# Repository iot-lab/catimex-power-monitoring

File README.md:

# Catimex: Hardware

Custom developer board for measure the power consumption of a load connected in either the USB connector or in the HOUT header connector.

## Overview
This folder contains the necessary files to replicate the custom board develop for catimex project. This board has the following features:
* [STM32F103RE Microcontroller](https://www.st.com/en/microcontrollers/stm32f103re.html)
* [FT2232H USB Bridge](https://www.ftdichip.com/Support/Documents/DataSheets/ICs/DS_FT2232H.pdf)
* [INA226 Power monitor](http://www.ti.com/product/INA226)

The board has two different power supply, one for the load (open-node) and other for the main microcontroller (control-node). In the picture below, the micro usb connector of the open node is marked in blue, while the connector for the control node is marked in a red rectangle.

In this version the jumper in 3V3 must be placed to power the control node.

## How to use

### Power the board
#### From a usb port
To measure the power consumption of any load, connect two micro usb ports to each connector. The control node will send the information through serial port so you need to connect this to a pc. On the other side you can power the open node from a pc usb port or any other source.

#### From an external source
If you do not want to connect the control node to a pc, you can connect a battery in the JST connector on the board and access to serial port through the pin headers exposed on the board.

### Connect the load
The load or open-node should be connected in the usb connector or in the HOUT header connector. Once plug in you should start to receive the measurement of bus voltage and current used by the board.

### Power Supply and Start-up Considerations
The board available connectors are:
* USBCN : USB connector for the control node. If connected the control node is power up and you will be able to receive through serial console.
* USBON : USB connector for power up and interact with any node connected, in this case the open node.
* USB : USB port to connect a external node, as in this case the open node
* HOUT : Header to power an external node (open node) from a header connector instead of using the USB port above.
* BAT : Header connector to plug any external battery for the open node, instead of use USBON connection.
* BAT-JST : JST connector to plug in an external battery
* 3V3_IN : Feed the control node from the on-board voltage regulator and USBCN. A jumper has to be connecting both pins in order to power the control node from USB port. Note: This was build for development purposes.

The pinout configuration is in the image below:

## Need features
From the different test made, there are the following missing features:
* Add 2 LEDs to the board
* Add an OFF state for power the open node
* Match I2C port for INA226 with current in FIT IoTLab and the ALERT interrupt pin
* Add a battery charger
* Be able to put a 802.15.4 radio on top
* Expose same pins as the control node in FIT
* Be able to measure voltage of battery

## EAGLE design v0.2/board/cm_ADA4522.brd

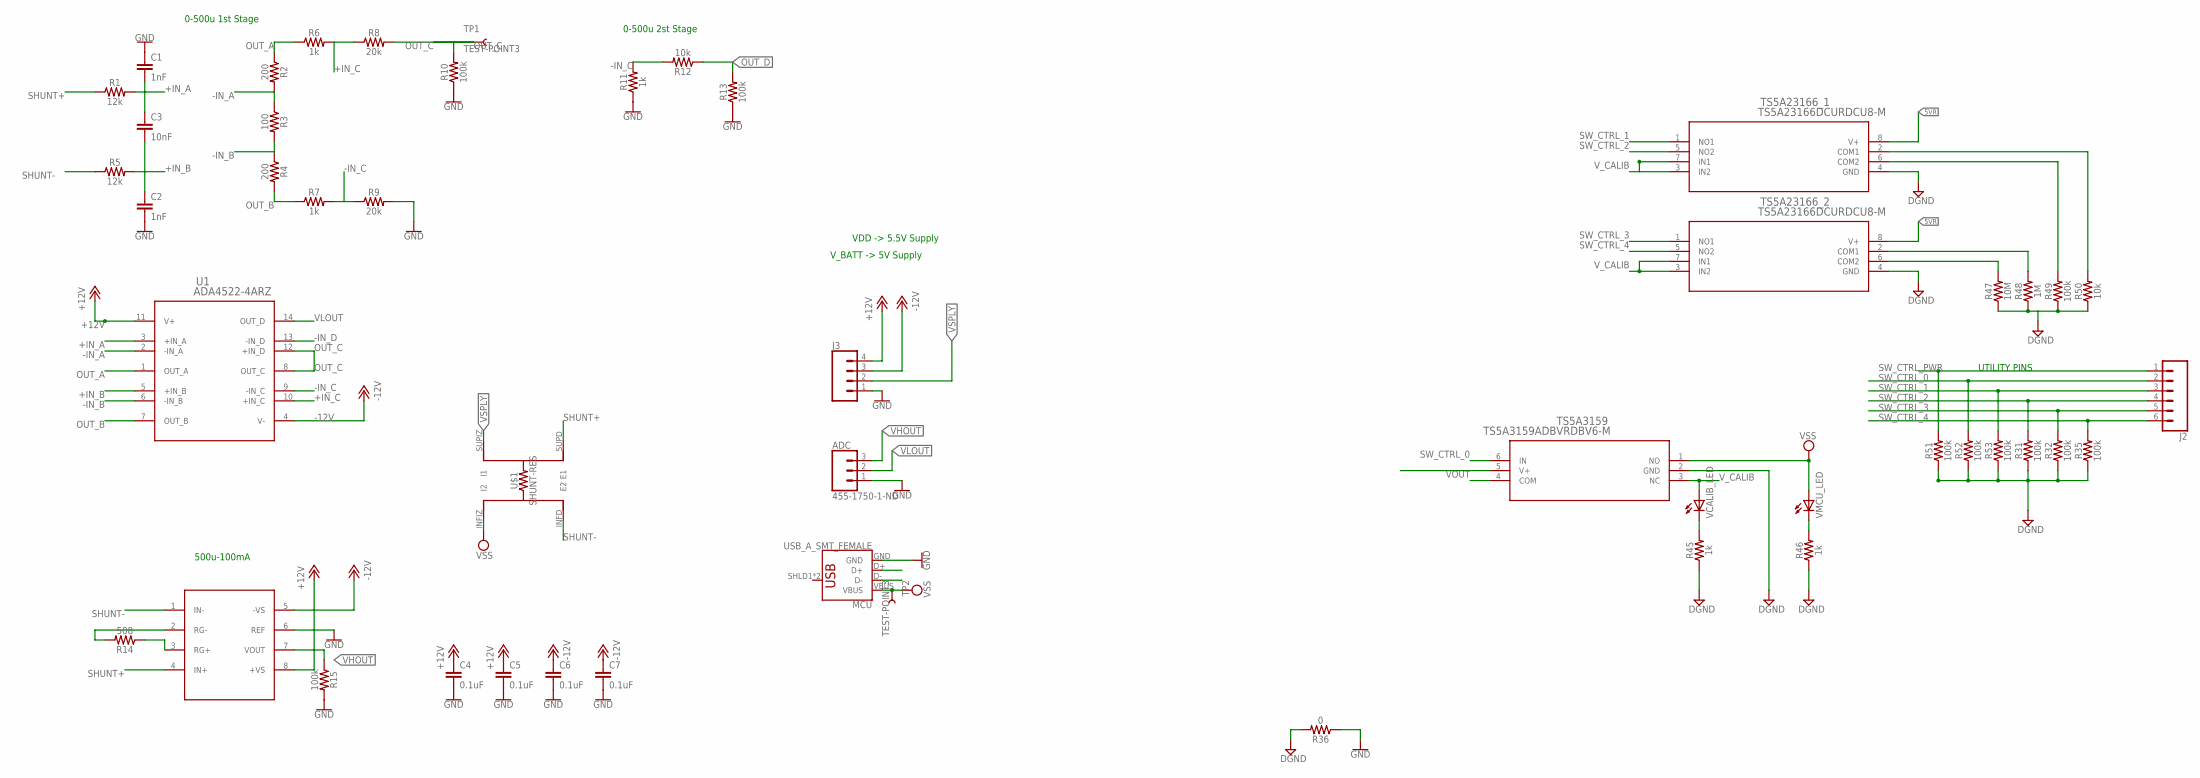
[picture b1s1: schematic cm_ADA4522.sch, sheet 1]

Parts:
AD8422: AD8422; SO08
ADC: 455-1750-1-ND; 1X03
C1, C2: 1nF; 0603
C3: 10nF; 0603
C4, C5, C6, C7: 0.1uF; 0603
J2: CONN_06LONGPADS; 1X06_LONGPADS
J3: CONN_04; 1X04
MCU: USB_A_SMT_FEMALE; USB-A-S-SILK-FEMALE
R1, R5: 12k; 0603
R2, R4: 200; 0603
R3: 100; 0603
R6, R7, R11, R45, R46: 1k; 0603
R8, R9: 20k; 0603
R10, R13, R15, R31, R32, R35, R49, R51, R52, R53: 100k; 0603
R12, R50: 10k; 0603
R14: 508; 0603
R36: 0; 0603
R47: 10M; 0603
R48: 1M; 0603
TP1, TP2: TEST-POINT3; PAD.03X.03
TS5A3159: TS5A3159ADBVRDBV6-M; DBV6-M
TS5A23166_1, TS5A23166_2: TS5A23166DCURDCU8-M; DCU8-M
U1: ADA4522-4ARZ; R_14
U$1: SHUNT-RES; HIPREC-SMD-SHUNT
VCALIB_LED: LEDCHIPLED_0603; CHIPLED_0603
VMCU_LED: LEDCHIPLED_0603; CHIPLED_0603

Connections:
5VR: TS5A23166_1.8 (V+), TS5A23166_2.8 (V+); also elsewhere on the board
5V_F: TS5A3159.5 (V+)
+12V: AD8422.8 (+VS), C4.1, C5.1, J3.4, U1.11 (V+); also elsewhere on the board
+IN_A: C1.2, C3.1, R1.2, U1.3 (+IN_A)
+IN_B: C2.1, C3.2, R5.2, U1.5 (+IN_B)
+IN_C: R6.2, R8.1, U1.10 (+IN_C)
-12V: AD8422.5 (-VS), C6.1, C7.1, J3.3, U1.4 (V-); also elsewhere on the board
-IN_A: R2.2, R3.1, U1.2 (-IN_A)
-IN_B: R3.2, R4.1, U1.6 (-IN_B)
-IN_C: R7.2, R9.1, R11.2, R12.2, U1.9 (-IN_C)
-IN_D: U1.13 (-IN_D)
DGND: R31.1, R32.1, R35.1, R36.2, R45.1, R46.1, R47.1, R48.1, R49.1, R50.1, R51.1, R52.1, R53.1, TS5A3159.2 (GND), TS5A23166_1.4 (GND), TS5A23166_2.4 (GND); also elsewhere on the board
GND: AD8422.6 (REF), ADC.1, C1.1, C2.2, C4.2, C5.2, C6.2, C7.2, J3.1, MCU.GND, R9.2, R10.1, R11.1, R13.1, R15.2, R36.1; also elsewhere on the board
unnamed: AD8422.2 (RG-), R14.2
unnamed: AD8422.3 (RG+), R14.1
unnamed 36: R45.2, VCALIB_LED.C; also elsewhere on the board
unnamed 37: R46.2, VMCU_LED.C; also elsewhere on the board
unnamed: R50.2, TS5A23166_1.2 (COM1)
unnamed: R49.2, TS5A23166_1.6 (COM2)
unnamed: R48.2, TS5A23166_2.2 (COM1)
unnamed: R47.2, TS5A23166_2.6 (COM2)
OUT_A: R2.1, R6.1, U1.1 (OUT_A)
OUT_B: R4.2, R7.1, U1.7 (OUT_B)
OUT_C: R8.2, R10.2, TP1.P$1, U1.8 (OUT_C), U1.12 (+IN_D)
OUT_D: R12.1, R13.2
SHUNT+: AD8422.4 (IN+), R1.1, U$1.SUPD (E1)
SHUNT-: AD8422.1 (IN-), R5.1, U$1.INFD (E2)
SW_CTRL_0: J2.2, R52.2, TS5A3159.6 (IN); also elsewhere on the board
SW_CTRL_1: J2.3, R53.2, TS5A23166_1.1 (NO1); also elsewhere on the board
SW_CTRL_2: J2.4, R31.2, TS5A23166_1.5 (NO2); also elsewhere on the board
SW_CTRL_3: J2.5, R32.2, TS5A23166_2.1 (NO1); also elsewhere on the board
SW_CTRL_4: J2.6, R35.2, TS5A23166_2.5 (NO2); also elsewhere on the board
SW_CTRL_PWR: J2.1, R51.2; also elsewhere on the board
VHOUT: AD8422.7 (VOUT), ADC.3, R15.1
VLOUT: ADC.2, U1.14 (OUT_D)
VOUT: TS5A3159.4 (COM)
VSPLY: J3.2, U$1.SUPIZ (I1); also elsewhere on the board
VSS: MCU.VBUS, TP2.P$1, TS5A3159.1 (NO), U$1.INFIZ (I2), VMCU_LED.A; also elsewhere on the board
V_CALIB: TS5A3159.3 (NC), TS5A23166_1.3 (IN2), TS5A23166_1.7 (IN1), TS5A23166_2.3 (IN2), TS5A23166_2.7 (IN1), VCALIB_LED.A; also elsewhere on the board

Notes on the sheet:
0-500u 1st Stage
500u-100mA
0-500u 2st Stage
VDD -> 5.5V Supply
V_BATT -> 5V Supply
UTILITY PINS

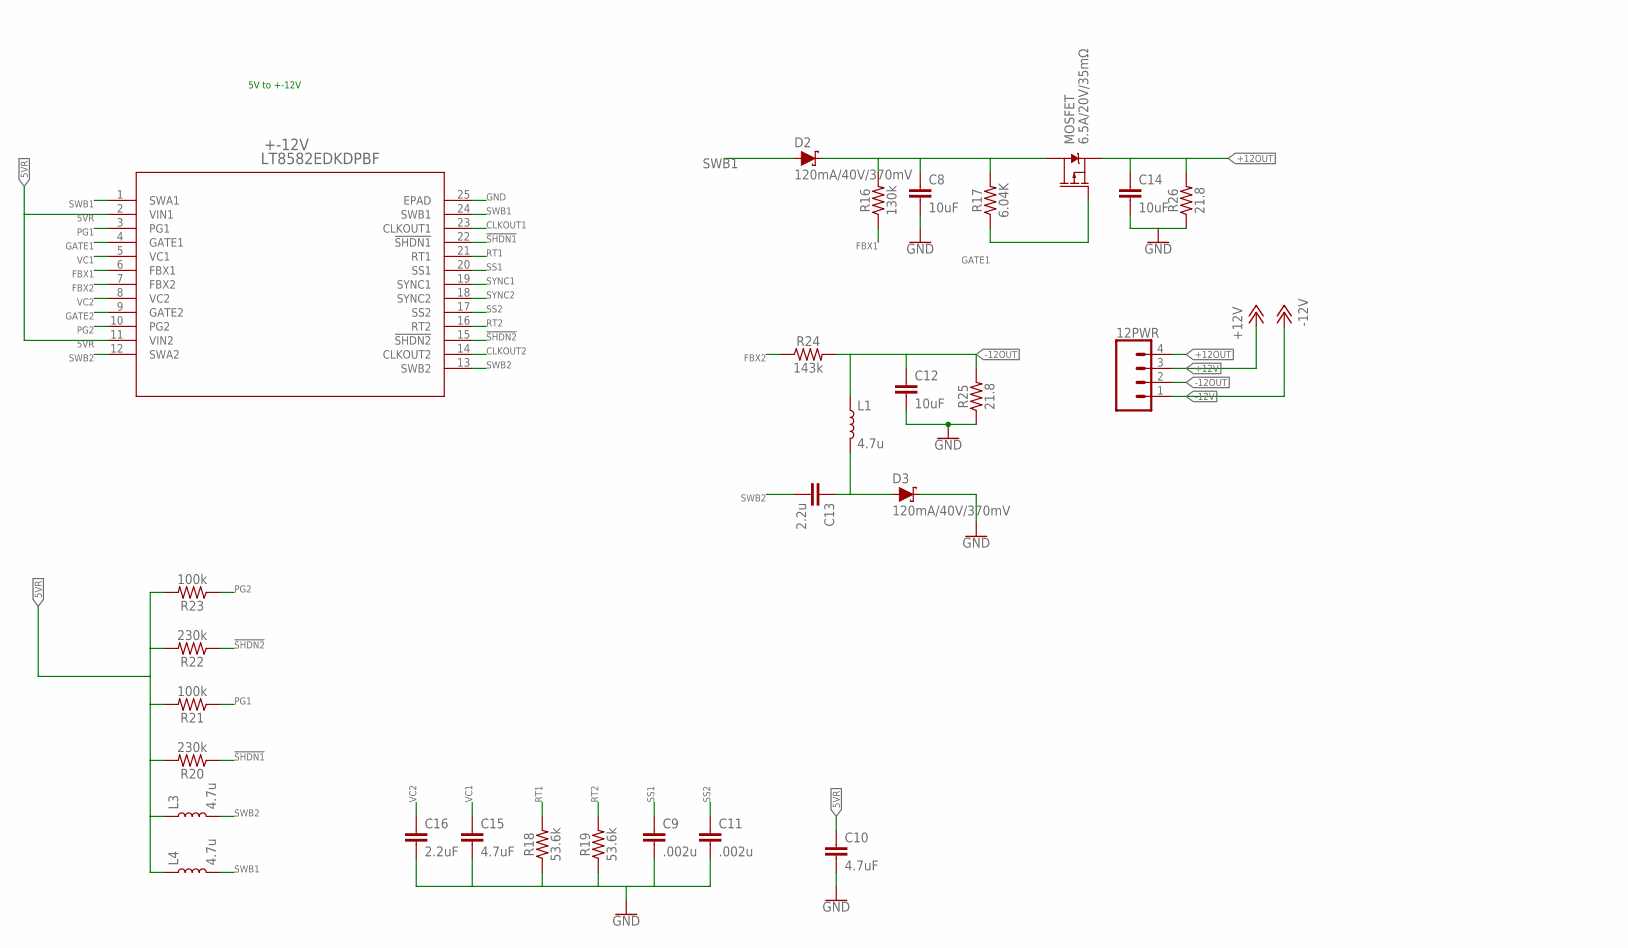
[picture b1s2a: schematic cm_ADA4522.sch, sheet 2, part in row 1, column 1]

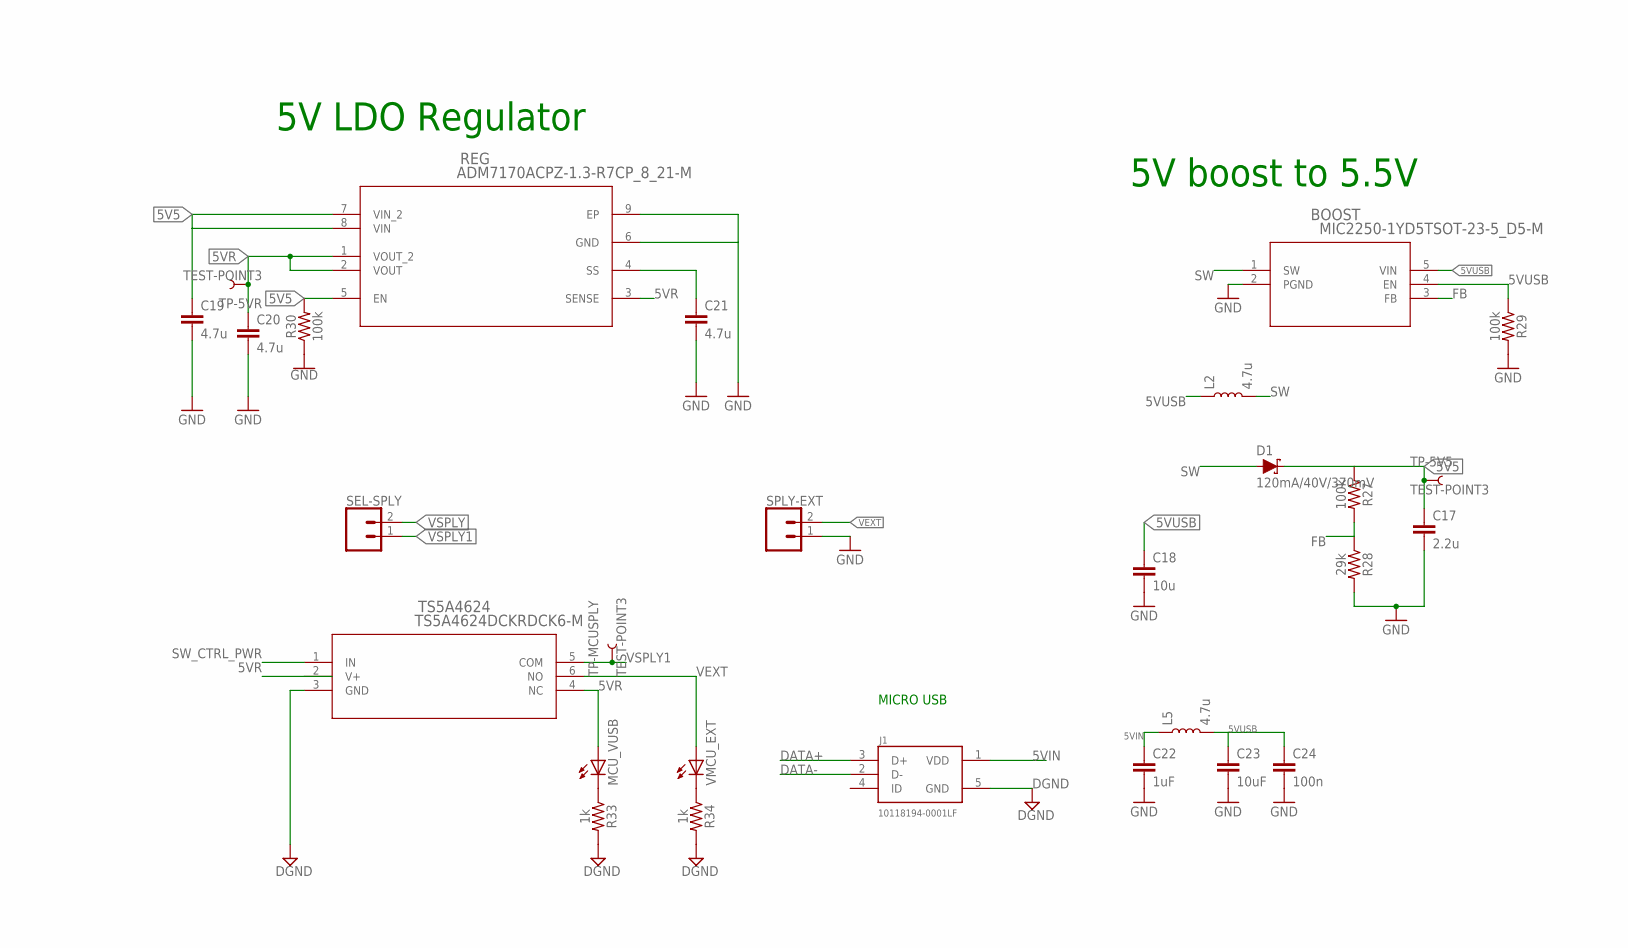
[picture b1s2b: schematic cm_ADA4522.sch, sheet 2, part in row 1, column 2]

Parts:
12PWR: CONN_04; 1X04
+-12V: LT8582EDKDPBF; DFN-24_DKD
BOOST: MIC2250-1YD5TSOT-23-5_D5-M; TSOT-23-5_D5-M
C8, C12, C14, C23: 10uF; 0603
C9, C11: .002u; 0603
C10, C15: 4.7uF; 0603
C13, C17: 2.2u; 0603
C16: 2.2uF; 0603
C18: 10u; 0603
C19, C20, C21: 4.7u; 0603
C22: 1uF; 0603
C24: 100n; 0603
D1, D2, D3: 120mA/40V/370mV; SOD-523
J1: 10118194-0001LF; FRAMATOME_10118194-0001LF
L1, L2, L3, L4, L5: 4.7u; 252012C
MCU_VUSB: LEDCHIPLED_0603; CHIPLED_0603
MOSFET: 6.5A/20V/35mΩ; SO08
R16: 130k; 0603
R17: 6.04K; 0603
R18, R19: 53.6k; 0603
R20, R22: 230k; 0603
R21, R23, R27, R29, R30: 100k; 0603
R24: 143k; 0603
R25, R26: 21.8; 0603
R28: 29k; 0603
R33, R34: 1k; 0603
REG: ADM7170ACPZ-1.3-R7CP_8_21-M; CP_8_21-M
SEL-SPLY: CONN_02; 1X02
SPLY-EXT: CONN_02; 1X02
TP-5V5, TP-5VR: TEST-POINT3; PAD.03X.03
TP-MCUSPLY: TEST-POINT3; PAD.03X.03
TS5A4624: TS5A4624DCKRDCK6-M; DCK6-M
VMCU_EXT: LEDCHIPLED_0603; CHIPLED_0603

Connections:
5V5: C17.1, C19.1, D1.C, R27.1, R30.2, REG.5 (EN), REG.7 (VIN_2), REG.8 (VIN), TP-5V5.P$1
5VIN: C22.1, J1.1 (VDD), L5.1; also elsewhere on the board
5VR: +-12V.2 (VIN1), +-12V.11 (VIN2), C10.1, C20.1, L3.1, L4.1, MCU_VUSB.A, R20.2, R21.2, R22.2, R23.2, REG.1 (VOUT_2), REG.2 (VOUT), REG.3 (SENSE), TP-5VR.P$1, TS5A4624.2 (V+), TS5A4624.4 (NC); also elsewhere on the board
5VUSB: BOOST.4 (EN), BOOST.5 (VIN), C18.1, C23.1, C24.1, L2.1, L5.2, R29.1
!SHDN1: +-12V.22 (!SHDN1), R20.1
!SHDN2: +-12V.15 (!SHDN2), R22.1
+12OUT: 12PWR.4, C14.1, MOSFET.1 (S), MOSFET.2 (S), MOSFET.3 (S), R26.2
+12V: 12PWR.3; also elsewhere on the board
-12OUT: 12PWR.2, C12.1, L1.1, R24.2, R25.2
-12V: 12PWR.1; also elsewhere on the board
CLKOUT1: +-12V.23 (CLKOUT1)
CLKOUT2: +-12V.14 (CLKOUT2)
DGND: J1.5 (GND), R33.2, R34.2, TS5A4624.3 (GND); also elsewhere on the board
FB: BOOST.3 (FB), R27.2, R28.1
FBX1: +-12V.6 (FBX1), R16.1
FBX2: +-12V.7 (FBX2), R24.1
GATE1: +-12V.4 (GATE1), MOSFET.4 (G), R17.1
GATE2: +-12V.9 (GATE2)
GND: +-12V.25 (EPAD), BOOST.2 (PGND), C8.2, C9.2, C10.2, C11.2, C12.2, C14.2, C15.2, C16.2, C17.2, C18.2, C19.2, C20.2, C21.2, C22.2, C23.2, C24.2, D3.C, R18.1, R19.1, R25.1, R26.1, R28.2, R29.2, R30.1, REG.6 (GND), REG.9 (EP), SPLY-EXT.1; also elsewhere on the board
unnamed 31: MCU_VUSB.C, R33.1; also elsewhere on the board
unnamed: C8.1, D2.C, MOSFET.5 (D), MOSFET.6 (D), MOSFET.7 (D), MOSFET.8 (D), R16.2, R17.2
unnamed: C13.1, D3.A, L1.2
unnamed 34: R34.1, VMCU_EXT.C; also elsewhere on the board
unnamed: C21.1, REG.4 (SS)
PG1: +-12V.3 (PG1), R21.1
PG2: +-12V.10 (PG2), R23.1
RT1: +-12V.21 (RT1), R18.2
RT2: +-12V.16 (RT2), R19.2
SS1: +-12V.20 (SS1), C9.1
SS2: +-12V.17 (SS2), C11.1
SW: BOOST.1 (SW), D1.A, L2.2
SWB1: +-12V.1 (SWA1), +-12V.24 (SWB1), D2.A, L4.2
SWB2: +-12V.12 (SWA2), +-12V.13 (SWB2), C13.2, L3.2
SW_CTRL_PWR: TS5A4624.1 (IN); also elsewhere on the board
SYNC1: +-12V.19 (SYNC1)
SYNC2: +-12V.18 (SYNC2)
VC1: +-12V.5 (VC1), C15.1
VC2: +-12V.8 (VC2), C16.1
VEXT: SPLY-EXT.2, TS5A4624.6 (NO), VMCU_EXT.A; also elsewhere on the board
VSPLY: SEL-SPLY.2; also elsewhere on the board
VSPLY1: SEL-SPLY.1, TP-MCUSPLY.P$1, TS5A4624.5 (COM)

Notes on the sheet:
5V to +-12V
5V boost to 5.5V
5V LDO Regulator
MICRO USB

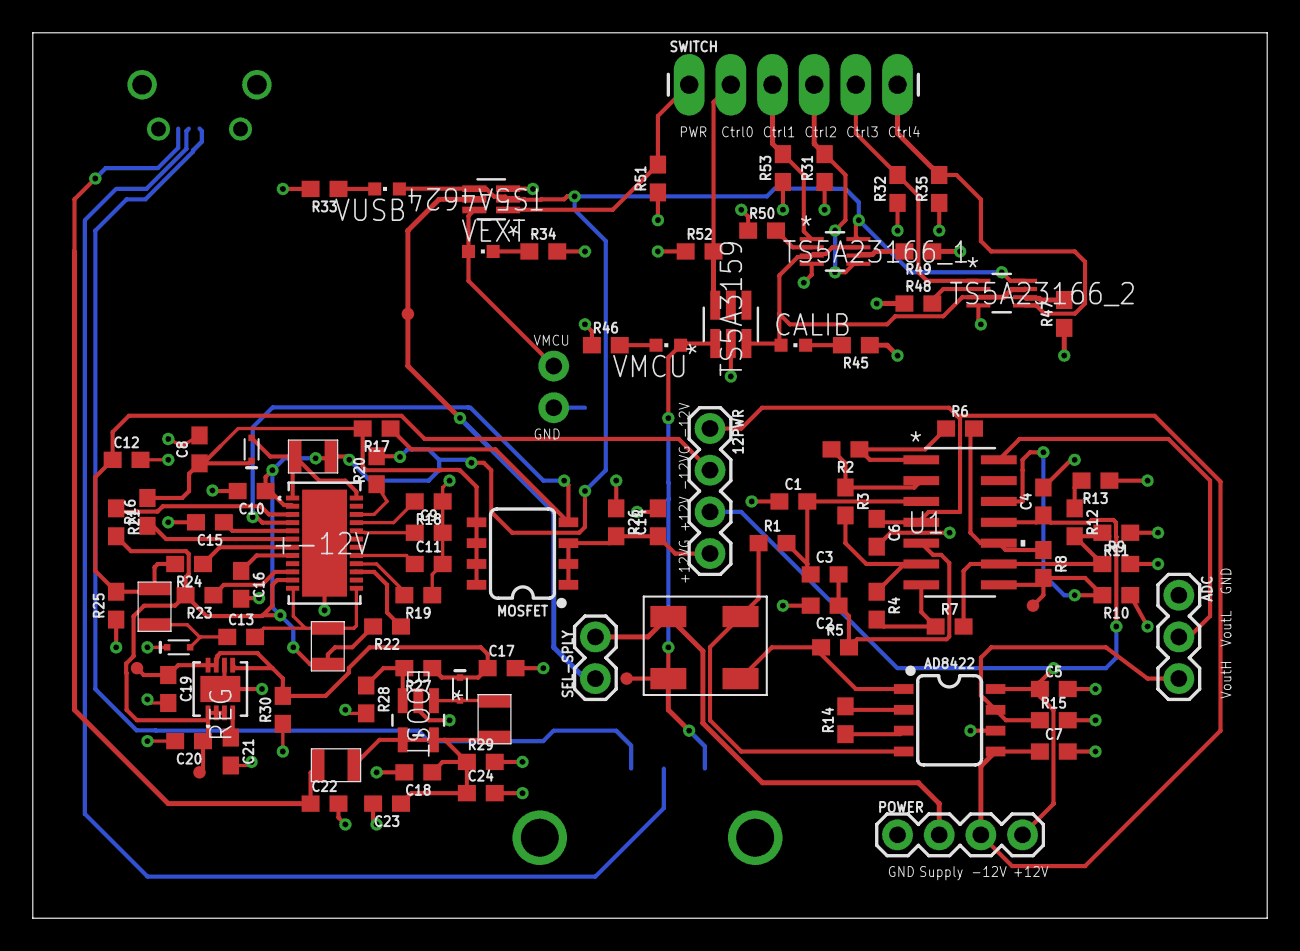
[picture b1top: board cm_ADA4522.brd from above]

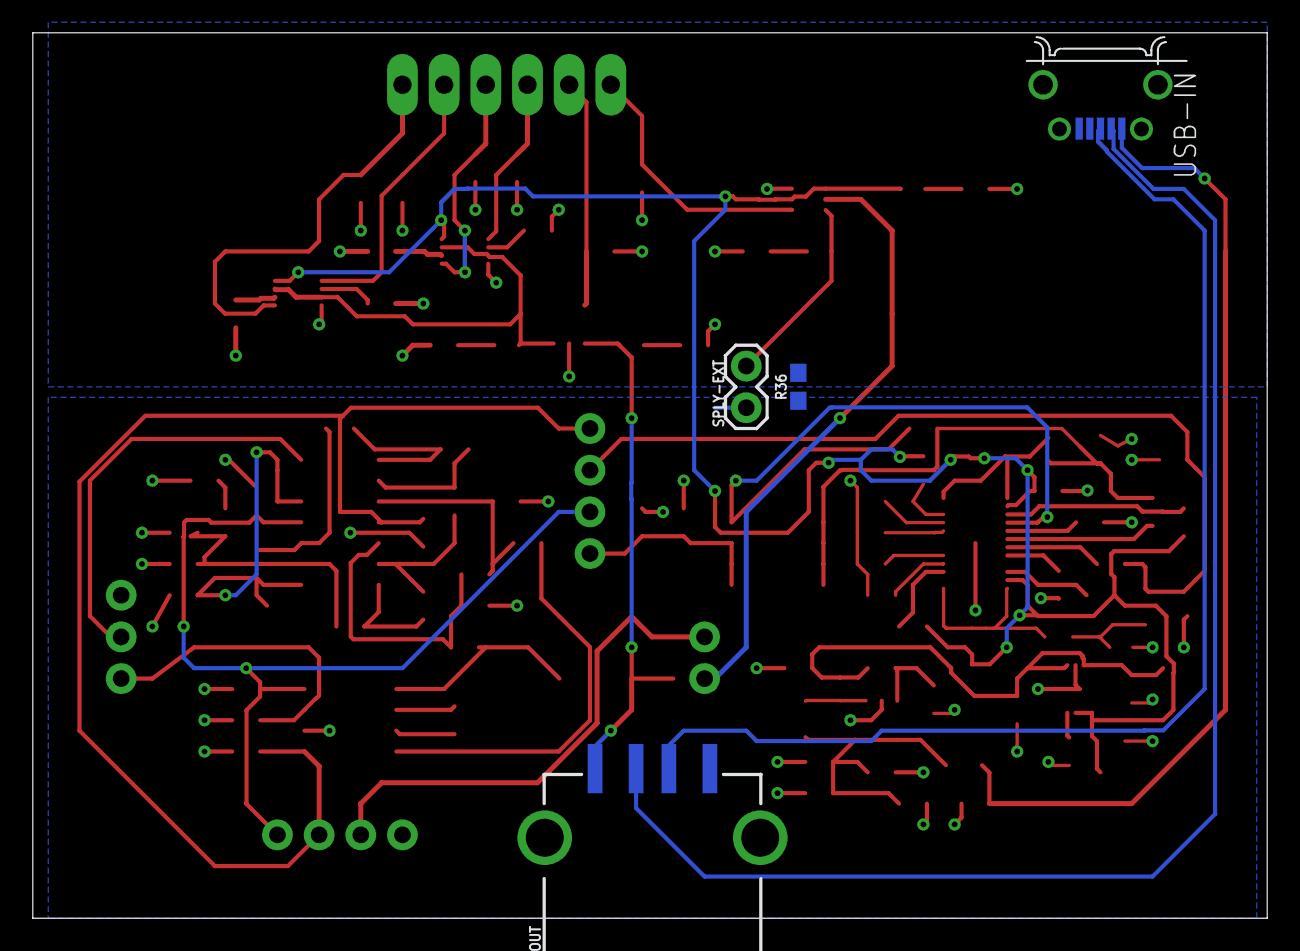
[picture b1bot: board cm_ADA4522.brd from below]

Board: 2 copper layers, 75.2 x 54.0 mm, 105 parts (4 on the bottom side), 67 nets.

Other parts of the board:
CALIB: CHIPLED_0603
POWER: 1X04
SWITCH: 1X06_LONGPADS
USB-IN: 10118194-0001LF; FRAMATOME_10118194-0001LF
USB-OUT: USB_A_SMT_FEMALE; USB-A-S-SILK-FEMALE
VEXT: CHIPLED_0603
VMCU: CHIPLED_0603
VUSB: CHIPLED_0603

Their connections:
5VIN: USB-IN.1; also elsewhere on the board
5VR: VUSB.A; also elsewhere on the board
+12V: POWER.4; also elsewhere on the board
-12V: POWER.3; also elsewhere on the board
DATA+: USB-IN.3, USB-OUT.D+
DATA-: USB-IN.2, USB-OUT.D-
DGND: USB-IN.5; also elsewhere on the board
GND: POWER.1, USB-OUT.GND; also elsewhere on the board
unnamed 31: VUSB.C; also elsewhere on the board
unnamed 34: VEXT.C; also elsewhere on the board
unnamed 36: CALIB.C; also elsewhere on the board
unnamed 37: VMCU.C; also elsewhere on the board
SW_CTRL_0: SWITCH.2; also elsewhere on the board
SW_CTRL_1: SWITCH.3; also elsewhere on the board
SW_CTRL_2: SWITCH.4; also elsewhere on the board
SW_CTRL_3: SWITCH.5; also elsewhere on the board
SW_CTRL_4: SWITCH.6; also elsewhere on the board
SW_CTRL_PWR: SWITCH.1; also elsewhere on the board
VEXT: VEXT.A; also elsewhere on the board
VSPLY: POWER.2; also elsewhere on the board
VSS: USB-OUT.VBUS, VMCU.A; also elsewhere on the board
V_CALIB: CALIB.A; also elsewhere on the board

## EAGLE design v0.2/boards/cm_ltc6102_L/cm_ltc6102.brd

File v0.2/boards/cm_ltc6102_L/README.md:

# PCB eagle for LTC6102 based current measurement board

### Some notation
* current measuring board (CMB): the designed circuit that measure shunt voltage, and supply voltage.
* mcu: the microcontroller that is connect to the CMB, performs calibrations and converts the supply voltage and current measurements.
* node: the target mcu which pwoer consumption the CMB is measuring.

### How to use

* connect switch controllers (SW0 to SW4) to 5 different GPIO on any mcu.
* if you wan't to control what supply is used for the node connect SW_PWR
* connect the ADC_CM_LOW to and ADC pin on your mcu
* connect INA226 sda and scl to your mcu sda and scl pins, PU ressitors are supplied in this board
* alert pin of INA226 is supplied, not used by default
* power the CMB by either connecting it to it's microUSB port ore the 5V supply pin.
* bypass the targeted node power supply by either connecting it's power source to VEXT or the USB port on CMB.
* if the targeted node supply source is connected to VEXT then the node can be powered by connecting it's power input to VMCU. By default the mcu will be supplied from the USB. SW_CTRL_PWR allows the user to select which.

### Ratings:
- Power supply: 5V from USB or 5V from external supply
- First Low range stage gain x1000.
- Second Low range stage gain x11.
- Ina226 for High current range 82mA-250uA
- LTC6102 for Low current range 250ua-0.01uA

#### Input Output pins

Multiple input/output pins are supplied (There are PD resistors so calibration resistors and node supply are normally turned off). These are:

- SW_PWR: switch between VEXT and VUSB for supplying node.
- SW0: switch between calibration mode and suplying node.
- SW1-4: switches on or off calibration resistors.
- VMCU: output voltage that powers the targeted node it's short-circuited to the female type A USB.
- GND: ground
- ADC: low current value tu be read by mcu ADC
- SDA/SCL: I2C wire connection to read INA226 voltage and current values
- VEXT: external supply oint for node, eg: a battery
- +5V: 5V input/output depending on operation

#### Jumper

- A jumpers enables or not the use of the regulated 5V power supply, if not the filtered USB supply powers all the CMB IC's

#### Test Pads

Multiple test pads have been exposed for board testing

- 5V_F: filter 5V usb supply
- 5.5V: output of boost stage
- 5VR: 5 vols LDO output
- Vin: voltage that comes in to 4-terminal shunt current in pad
- Vout: voltage that comes out of 4-terminal shunt current out pad
- SHUNT+: voltage that comes form 4-terminal shunt voltage+ read pad
- SHUNT-: voltage that comes form 4-terminal shunt voltage- read pad

#### Leds

The board has 6 status Leds:

- MCU_VUSB_LED: indicates if node is supplied from USB
- MCU_EXT_LED: indicates if node is supplied from external supply
- VCALID_LED: indicates if in calibration mode
- VMCU_LED: indicates if in normal mode
- USB_LED: if usb is connected
- 5V_LED: if regultor is on

# Board versions

## LTC6102 v0

### Details

Analog and digital ground are joined in star way.

USB supply is filterd threw a ferrite, every precisión IC is also isolated threw a ferrite.

USB enclosure is connected to the digital ground.

### Prototyping and testing conclusion

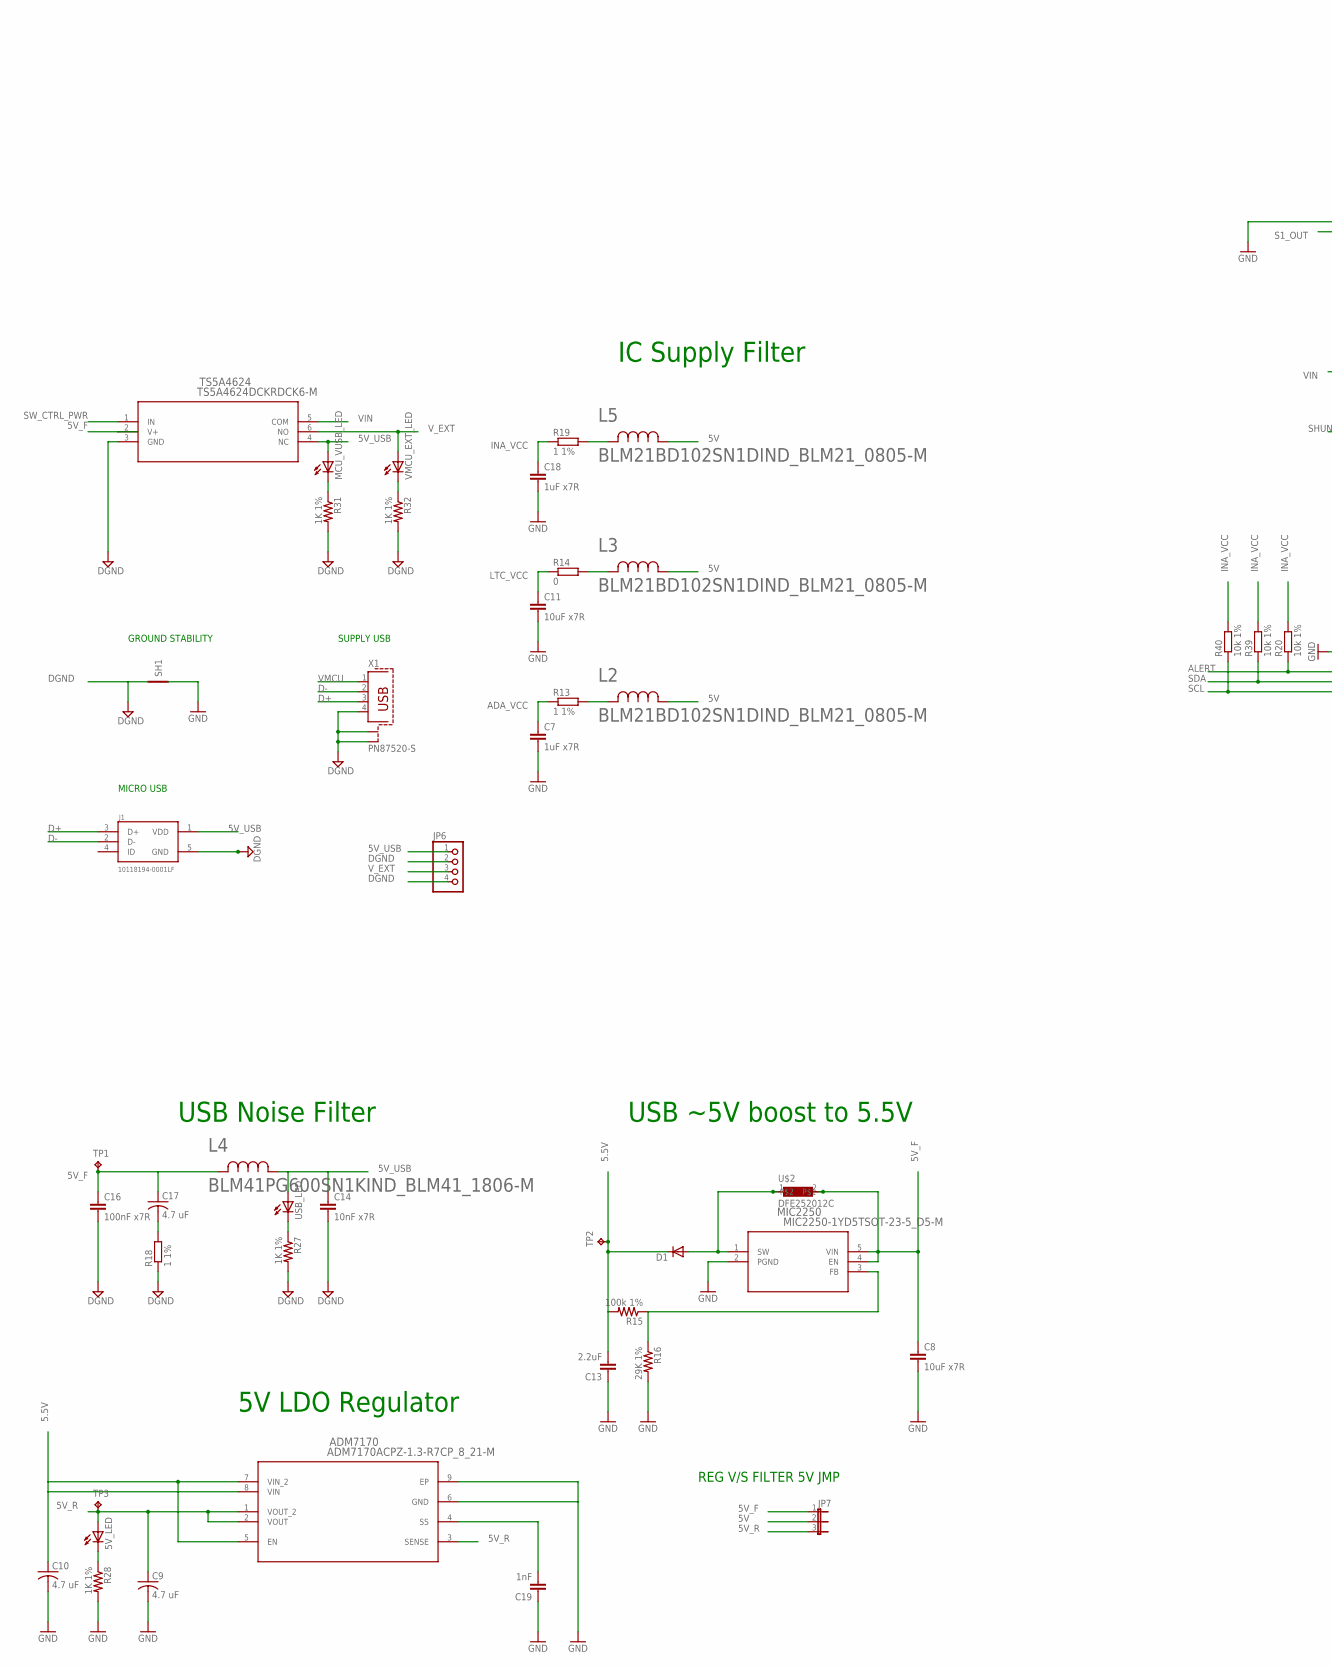
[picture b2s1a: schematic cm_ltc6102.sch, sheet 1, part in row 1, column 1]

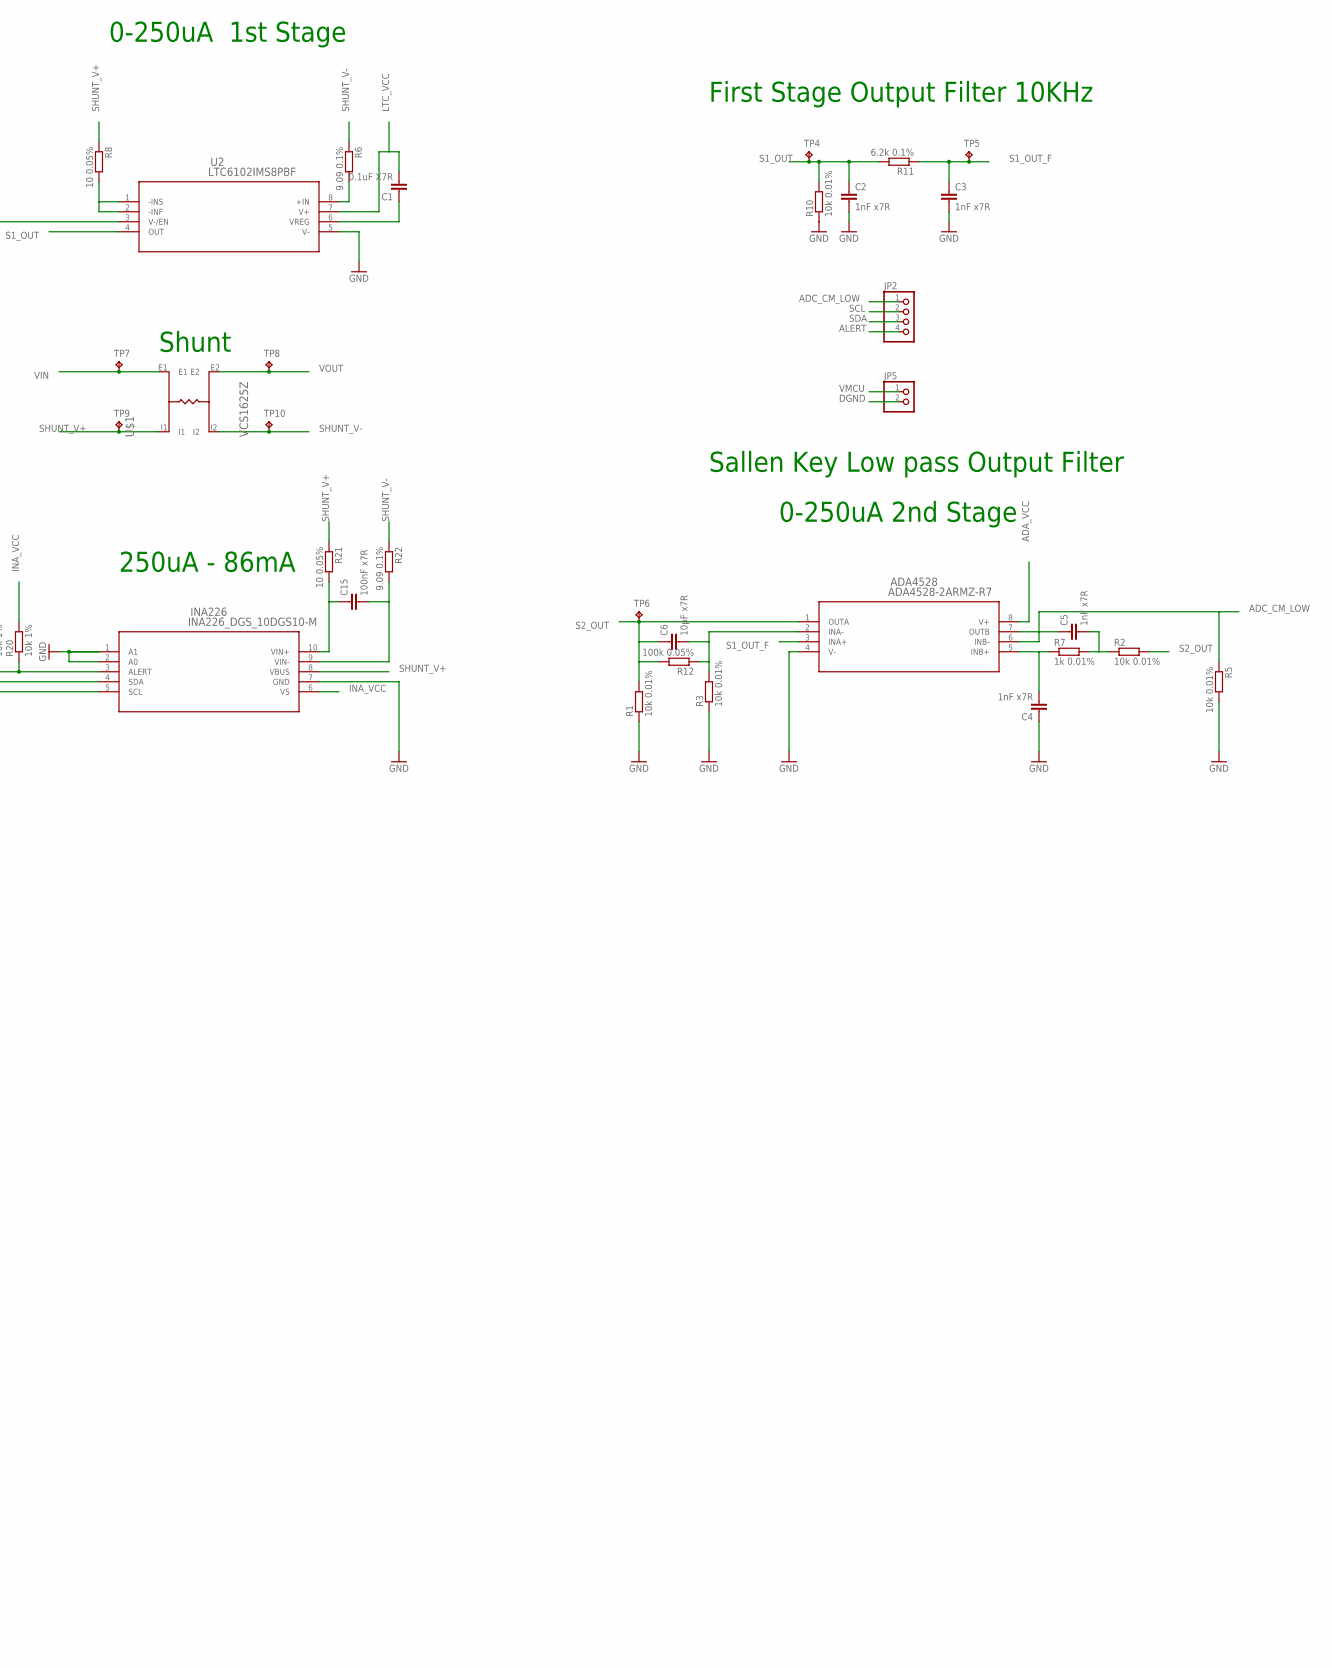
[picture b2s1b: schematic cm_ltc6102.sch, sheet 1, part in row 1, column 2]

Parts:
5V_LED: LEDCHIPLED_0603; CHIPLED_0603
ADA4528: ADA4528-2ARMZ-R7; RM_8
ADM7170: ADM7170ACPZ-1.3-R7CP_8_21-M; CP_8_21-M
C1: 0.1uF X7R; C0805
C2, C3, C4, C5: 1nF x7R; C0603
C6: 10pF x7R; C0603
C7, C18: 1uF x7R; C0603
C8, C11: 10uF x7R; C0805
C9, C10, C17: 4.7 uF; C1206
C13: 2.2uF; C0603
C14: 10nF x7R; C0603
C15, C16: 100nF x7R; C0603
C19: 1nF; C0603
D1: DIODE-SOD80C; SOD80C
INA226: INA226_DGS_10DGS10-M; DGS10-M
J1: 10118194-0001LF; FRAMATOME_10118194-0001LF
JP2, JP6: PINHD-1X4; 1X04
JP5: PINHD-1X2; 1X02
JP7: JP2E; JP2
L2, L3, L5: BLM21BD102SN1DIND_BLM21_0805-M; IND_BLM21_0805-M
L4: BLM41PG600SN1KIND_BLM41_1806-M; IND_BLM41_1806-M
MCU_VUSB_LED: LEDCHIPLED_0603; CHIPLED_0603
MIC2250: MIC2250-1YD5TSOT-23-5_D5-M; TSOT-23-5_D5-M
R1, R2, R3, R5, R10: 10k 0.01%; R0603
R6, R22: 9.09 0.1%; R0603
R7: 1k 0.01%; R0805
R8, R21: 10 0.05%; R0603
R11: 6.2k 0.1%; R0603
R12: 100k 0.05%; R0603
R13, R18, R19: 1 1%; R0603
R14: 0; R0603
R15: 100k 1%; R0603
R16: 29K 1%; R0603
R20, R39, R40: 10k 1%; R0603
R27, R28, R31, R32: 1K 1%; R0603
SH1: SHORT-VT5; SHORT_TOP-50
TP1, TP2, TP3, TP4, TP5, TP6, TP7, TP8, TP9, TP10: TPPAD1-20; P1-20
TS5A4624: TS5A4624DCKRDCK6-M; DCK6-M
U2: LTC6102IMS8PBF; MSOP-8_MS
U$1: VCS1625Z
U$2: DFE252012C
USB_LED: LEDCHIPLED_0603; CHIPLED_0603
VMCU_EXT_LED: LEDCHIPLED_0603; CHIPLED_0603
X1: PN87520-S

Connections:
5.5V: ADM7170.5 (EN), ADM7170.7 (VIN_2), ADM7170.8 (VIN), C10.1, C13.2, D1.C, R15.2, TP2.TP
5V: JP7.2, L2.1, L3.1, L5.1
5V_F: C8.1, C16.1, C17.1, JP7.1, L4.2, MIC2250.4 (EN), MIC2250.5 (VIN), TP1.TP, TS5A4624.2 (V+), U$2.2; also elsewhere on the board
5V_R: 5V_LED.A, ADM7170.1 (VOUT_2), ADM7170.2 (VOUT), ADM7170.3 (SENSE), C9.1, JP7.3, TP3.TP
5V_USB: C14.1, J1.1 (VDD), JP6.1, L4.1, MCU_VUSB_LED.A, TS5A4624.4 (NC), USB_LED.A
ADA_VCC: ADA4528.8 (V+), C7.1, R13.1
ADC_CM_LOW: ADA4528.6 (INB-), ADA4528.7 (OUTB), C5.1, JP2.1, R5.1
ALERT: INA226.3 (ALERT), JP2.4, R20.1
D+: J1.3 (D+), X1.3
D-: J1.2 (D-), X1.2
DGND: C14.2, C16.2, J1.5 (GND), JP5.2, JP6.2, JP6.4, R18.1, R27.2, R31.2, R32.2, SH1.2, TS5A4624.3 (GND), X1.4, X1.S1, X1.S2; also elsewhere on the board
GND: ADA4528.4 (V-), ADM7170.6 (GND), ADM7170.9 (EP), C2.2, C3.2, C4.1, C7.2, C8.2, C9.2, C10.2, C11.2, C13.1, C18.2, C19.1, INA226.1 (A1), INA226.2 (A0), INA226.7 (GND), MIC2250.2 (PGND), R1.1, R3.1, R5.2, R10.1, R16.2, R28.2, SH1.1, U2.3 (V-/EN), U2.5 (V-)
INA_VCC: C18.1, INA226.6 (VS), R19.1, R20.2, R39.2, R40.2
unnamed: R8.2, U2.1 (-INS), U2.2 (-INF)
unnamed: R6.2, U2.8 (+IN)
unnamed: R27.1, USB_LED.C
unnamed: ADA4528.5 (INB+), C4.2, R7.1
unnamed: C5.2, R2.1, R7.2
unnamed: L3.2, R14.2
unnamed: D1.A, MIC2250.1 (SW), U$2.1
unnamed: ADA4528.2 (INA-), C6.2, R3.2, R12.1
unnamed: L2.2, R13.2
unnamed: C15.1, INA226.10 (VIN+), R21.2
unnamed: ADM7170.4 (SS), C19.2
unnamed: MIC2250.3 (FB), R15.1, R16.1
unnamed: C17.2, R18.2
unnamed: L5.2, R19.2
unnamed: C15.2, INA226.9 (VIN-), R22.2
unnamed: 5V_LED.C, R28.1
unnamed: MCU_VUSB_LED.C, R31.1
unnamed: R32.1, VMCU_EXT_LED.C
S1_OUT: C2.1, R10.2, R11.2, TP4.TP, U2.4 (OUT)
S1_OUT_F: ADA4528.3 (INA+), C3.1, R11.1, TP5.TP
S2_OUT: ADA4528.1 (OUTA), C6.1, R1.2, R2.2, R12.2, TP6.TP
SCL: INA226.5 (SCL), JP2.2, R40.1
SDA: INA226.4 (SDA), JP2.3, R39.1
SHUNT_V+: INA226.8 (VBUS), R8.1, R21.1, TP9.TP, U$1.I1
SHUNT_V-: R6.1, R22.1, TP10.TP, U$1.I2
SW_CTRL_PWR: TS5A4624.1 (IN); also elsewhere on the board
VIN: TP7.TP, TS5A4624.5 (COM), U$1.E1
VMCU: JP5.1, X1.1; also elsewhere on the board
VOUT: TP8.TP, U$1.E2; also elsewhere on the board
V_EXT: JP6.3, TS5A4624.6 (NO), VMCU_EXT_LED.A

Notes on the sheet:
USB Noise Filter
USB ~5V boost to 5.5V
5V LDO Regulator
IC Supply Filter
First Stage Output Filter 10KHz
Sallen Key Low pass Output Filter
0-250uA 2nd Stage
0-250uA 1st Stage
250uA - 86mA
Shunt
SUPPLY USB
MICRO USB
GROUND STABILITY
REG V/S FILTER 5V JMP

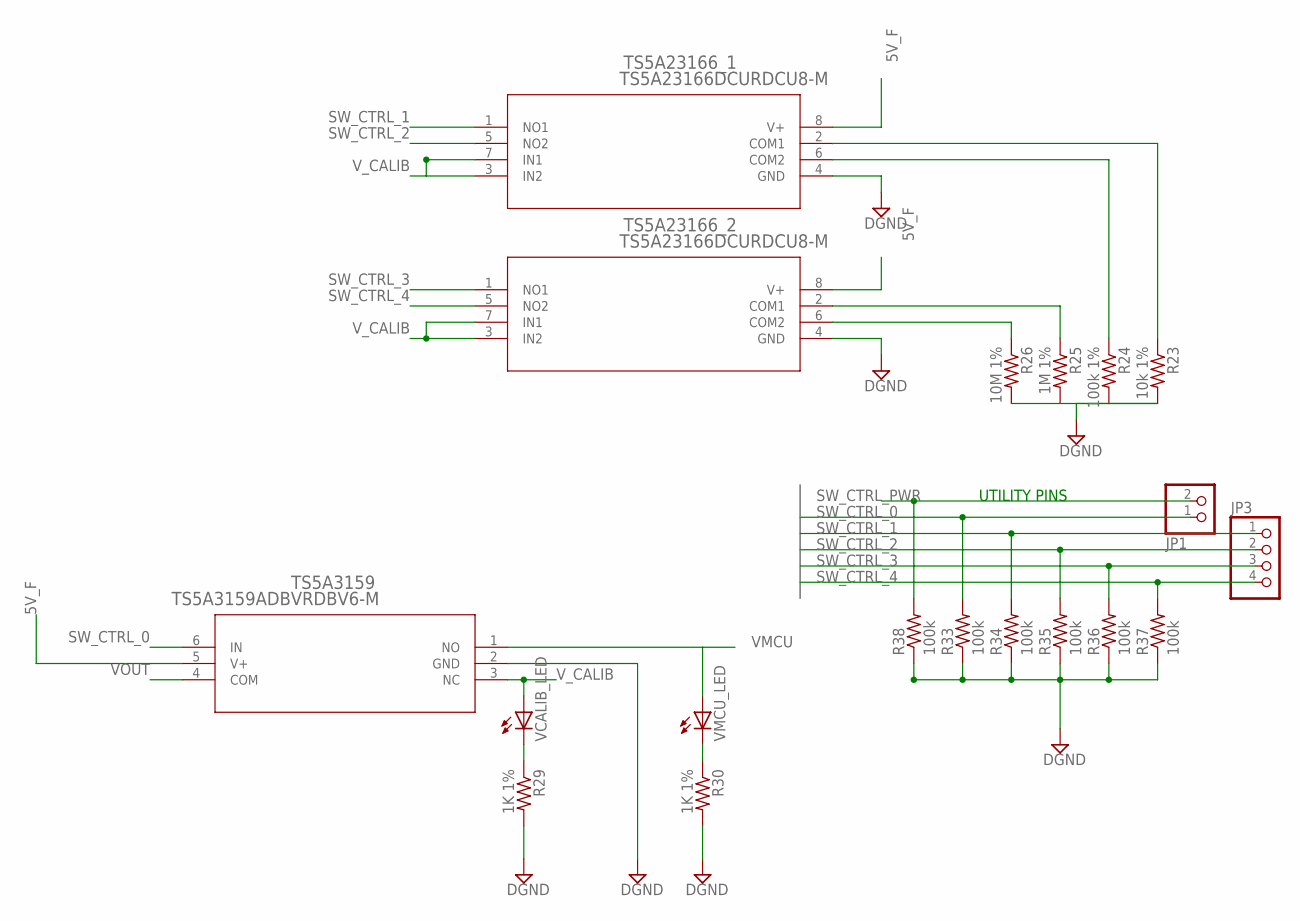
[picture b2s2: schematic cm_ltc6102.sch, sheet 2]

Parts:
JP1: PINHD-1X2; 1X02
JP3: PINHD-1X4; 1X04
R23: 10k 1%; R0603
R24: 100k 1%; R0603
R25: 1M 1%; R0603
R26: 10M 1%; R0603
R29, R30: 1K 1%; R0603
R33, R34, R35, R36, R37, R38: 100k; R0805
TS5A3159: TS5A3159ADBVRDBV6-M; DBV6-M
TS5A23166_1, TS5A23166_2: TS5A23166DCURDCU8-M; DCU8-M
VCALIB_LED: LEDCHIPLED_0603; CHIPLED_0603
VMCU_LED: LEDCHIPLED_0603; CHIPLED_0603

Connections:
5V_F: TS5A3159.5 (V+), TS5A23166_1.8 (V+), TS5A23166_2.8 (V+); also elsewhere on the board
DGND: R23.2, R24.2, R25.2, R26.2, R29.2, R30.2, R33.1, R34.1, R35.1, R36.1, R37.1, R38.1, TS5A3159.2 (GND), TS5A23166_1.4 (GND), TS5A23166_2.4 (GND); also elsewhere on the board
unnamed: R29.1, VCALIB_LED.C
unnamed: R30.1, VMCU_LED.C
unnamed: R23.1, TS5A23166_1.2 (COM1)
unnamed: R24.1, TS5A23166_1.6 (COM2)
unnamed: R25.1, TS5A23166_2.2 (COM1)
unnamed: R26.1, TS5A23166_2.6 (COM2)
SW_CTRL_0: JP1.1, R33.2, TS5A3159.6 (IN)
SW_CTRL_1: JP3.1, R34.2, TS5A23166_1.1 (NO1)
SW_CTRL_2: JP3.2, R35.2, TS5A23166_1.5 (NO2)
SW_CTRL_3: JP3.3, R36.2, TS5A23166_2.1 (NO1)
SW_CTRL_4: JP3.4, R37.2, TS5A23166_2.5 (NO2)
SW_CTRL_PWR: JP1.2, R38.2; also elsewhere on the board
VMCU: TS5A3159.1 (NO), VMCU_LED.A; also elsewhere on the board
VOUT: TS5A3159.4 (COM); also elsewhere on the board
V_CALIB: TS5A3159.3 (NC), TS5A23166_1.3 (IN2), TS5A23166_1.7 (IN1), TS5A23166_2.3 (IN2), TS5A23166_2.7 (IN1), VCALIB_LED.A

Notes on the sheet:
UTILITY PINS

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

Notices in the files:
parts and their libraries:
SparkFun-Connectors: Licensing: Creative Commons ShareAlike 4.0 International - https://creativecommons.org/licenses/by-sa/4.0
